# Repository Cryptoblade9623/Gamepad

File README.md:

# Gamepad
This is a keyboard with only 27 keys. It was designed for gaming, so only the keys that I need for games are included.
It has per-key RGB, and you can cycle through different animations with some combos I made.
It has a rotary encoder for volume control, and to mute something.
I am reusing many of the parts that I already have, so I will not include them in the BOM.
It is controlled and coded with CircuitPython with KMK and a Waveshare RP2040 Zero.
The files in the Files folder contain everything you need to make or edit it, like KiCad and Fusion 360 source files, Gerbers and firmware.

## BOM
| Item                     | Qty | Supplier   | Cost/item | Total Cost | link                                                                                                                                                                                                                                                                                                                                                                                                                                                                                                                                                                                                                                                                                                                                                                                                                                                                                                                           |
|--------------------------|-----|------------|-----------|------------|--------------------------------------------------------------------------------------------------------------------------------------------------------------------------------------------------------------------------------------------------------------------------------------------------------------------------------------------------------------------------------------------------------------------------------------------------------------------------------------------------------------------------------------------------------------------------------------------------------------------------------------------------------------------------------------------------------------------------------------------------------------------------------------------------------------------------------------------------------------------------------------------------------------------------------|
| Waveshare RP2040 Zero    | 1   | AliExpress | $3.22     | $3.22      | https://www.aliexpress.com/item/1005008738491752.html?spm=a2g0o.productlist.main.34.3f1d10600ni14G&algo_pvid=a21f30b3-3a94-43fc-8dde-88dda27b717c&algo_exp_id=a21f30b3-3a94-43fc-8dde-88dda27b717c-31&pdp_ext_f=%7B%22order%22%3A%22378%22%2C%22spu_best_type%22%3A%22price%22%2C%22eval%22%3A%221%22%2C%22fromPage%22%3A%22search%22%7D&pdp_npi=6%40dis%21USD%213.22%211.35%21%21%2121.38%218.96%21%4021613be817938165109603134e1081%2112000059443265566%21sea%21GB%210%21ABX%211%210%21n_tag%3A-29910%3Bd%3Ad6cd2d24%3Bm03_new_user%3A-29895%3BpisId%3A5000000218642851&curPageLogUid=lCmdrrr83lyW&utparam-url=scene%3Asearch%7Cquery_from%3A%7Cx_object_id%3A1005008738491752%7C_p_origin_prod%3A                                                                                                                                                                                                                           |
| SK6812 MINI E            | 1   | AliExpress | $3.89     | $3.89      | https://www.aliexpress.com/item/1005007804788253.html?spm=a2g0o.productlist.main.6.1a374166AxfWN4&algo_pvid=ce4f786e-61a2-4f07-85fa-2494f0c9bdd4&algo_exp_id=ce4f786e-61a2-4f07-85fa-2494f0c9bdd4-5&pdp_ext_f=%7B%22order%22%3A%2250%22%2C%22eval%22%3A%221%22%2C%22fromPage%22%3A%22search%22%7D&pdp_npi=6%40dis%21USD%213.89%213.89%21%21%213.89%213.89%21%402103810f17938167089143682e0d51%2112000042259509038%21sea%21GB%210%21ABX%211%210%21n_tag%3A-29910%3Bd%3Ad6cd2d24%3Bm03_new_user%3A-29895&curPageLogUid=SlNEr6LLqNnO&utparam-url=scene%3Asearch%7Cquery_from%3A%7Cx_object_id%3A1005007804788253%7C_p_origin_prod%3A                                                                                                                                                                                                                                                                                              |
| Custom PCB               | 1   | JLCPCB     | $10.90    | $10.90     | https://cart.jlcpcb.com/shopcart/cart/                                                                                                                                                                                                                                                                                                                                                                                                                                                                                                                                                                                                                                                                                                                                                                                                                                                                                         |
| 1N4148 Diodes            | 1   | AliExpress | $1.19     | $1.19      | https://www.aliexpress.com/item/1005007536719404.html?spm=a2g0o.detail.similar_items.1.d644K42vK42vpm&utparam-url=scene%3Aimage_search%7Cquery_from%3Aapp_pdp_sold_out%7Cx_object_id%3A1005007536719404%7C_p_origin_prod%3A&algo_pvid=a3281ef9-5730-48c4-893d-d7d506aeae6c&algo_exp_id=a3281ef9-5730-48c4-893d-d7d506aeae6c&pdp_ext_f=%7B%22order%22%3A%22306%22%2C%22spu_best_type%22%3A%22price%22%2C%22fromPage%22%3A%22search%22%7D&pdp_npi=6%40dis%21USD%211.28%211.19%21%21%218.53%217.93%21%4021613be817938177175121953e0fbc%2112000041199095476%21sea%21GB%210%21ABX%211%210%21n_tag%3A-29910%3Bd%3Ad6cd2d24%3Bm03_new_user%3A-29895%3BpisId%3A5000000220770329                                                                                                                                                                                                                                                        |
| USBC Breakout Board      | 1   | AliExpress | $1.13     | $1.13      | https://www.aliexpress.com/item/1005012011244259.html?spm=a2g0o.productlist.main.60.71a074621WW6ry&algo_pvid=724b5fb3-6e73-4c34-994f-f0d0a4bcf023&algo_exp_id=724b5fb3-6e73-4c34-994f-f0d0a4bcf023-57&pdp_ext_f=%7B%22order%22%3A%2267%22%2C%22eval%22%3A%221%22%2C%22fromPage%22%3A%22search%22%7D&pdp_npi=6%40dis%21USD%211.20%211.12%21%21%217.96%217.43%21%400b15841617938179246968172e0e1d%2112000057265199957%21sea%21GB%210%21ABX%211%210%21n_tag%3A-29910%3Bd%3Ad6cd2d24%3Bm03_new_user%3A-29895%3BpisId%3A5000000220770329&curPageLogUid=zSV1yswovQO5&utparam-url=scene%3Asearch%7Cquery_from%3A%7Cx_object_id%3A1005012011244259%7C_p_origin_prod%3A                                                                                                                                                                                                                                                                 |
| Stabilizers              | 1   | AliExpress | $4.51     | $4.51      | https://www.aliexpress.com/item/1005002003442544.html?spm=a2g0o.productlist.main.42.a17f2d96M7oa60&algo_pvid=f8edf524-10fd-4b72-87ca-8fe916213379&algo_exp_id=f8edf524-10fd-4b72-87ca-8fe916213379-37&pdp_ext_f=%7B%22order%22%3A%2256%22%2C%22eval%22%3A%221%22%2C%22fromPage%22%3A%22search%22%7D&pdp_npi=6%40dis%21USD%214.51%213.77%21%21%214.51%213.77%21%400b88ac1917939129812146151e0d1b%2112000033272651555%21sea%21GB%210%21ABX%211%210%21n_tag%3A-29910%3Bd%3Ad6cd2d24%3Bm03_new_user%3A-29895%3BpisId%3A5000000220905999&curPageLogUid=jusW35DST7r5&utparam-url=scene%3Asearch%7Cquery_from%3A%7Cx_object_id%3A1005002003442544%7C_p_origin_prod%3A                                                                                                                                                                                                                                                                 |
| Rubber Feet              | 1   | AliExpress | $1.23     | $1.23      | https://www.aliexpress.com/item/1005005828846290.html?spm=a2g0o.detail.pcDetailTopMoreOtherSeller.5.75ccCE3yCE3yFL&gps-id=pcDetailTopMoreOtherSeller&scm=1007.40050.354490.0&scm_id=1007.40050.354490.0&scm-url=1007.40050.354490.0&pvid=fc5e9689-4804-4616-a200-f08fdc2983ab&_t=gps-id%3ApcDetailTopMoreOtherSeller%2Cscm-url%3A1007.40050.354490.0%2Cpvid%3Afc5e9689-4804-4616-a200-f08fdc2983ab%2Ctpp_buckets%3A668%232846%238116%232002&pdp_ext_f=%7B%22order%22%3A%22466%22%2C%22eval%22%3A%221%22%2C%22sceneId%22%3A%2230050%22%2C%22fromPage%22%3A%22recommend%22%7D&pdp_npi=6%40dis%21USD%211.29%211.23%21%21%218.56%218.16%21%40210382de17939869266068634e0d1c%2112000034498446917%21rec%21GB%21%21ABX%211%210%21n_tag%3A-29910%3Bd%3Ad6cd2d24%3Bm03_new_user%3A-29895%3BpisId%3A5000000220905999&utparam-url=scene%3ApcDetailTopMoreOtherSeller%7Cquery_from%3A%7Cx_object_id%3A1005005828846290%7C_p_origin_prod%3A |
| Estimated total shipping |     |            |           | $6.66      |                                                                                                                                                                                                                                                                                                                                                                                                                                                                                                                                                                                                                                                                                                                                                                                                                                                                                                                                |
| Grand Total              |     |            |           | $32.73     |                                                                                                                                                                                                                                                                                                                                                                                                                                                                                                                                                                                                                                                                                                                                                                                                                                                                                                                                |

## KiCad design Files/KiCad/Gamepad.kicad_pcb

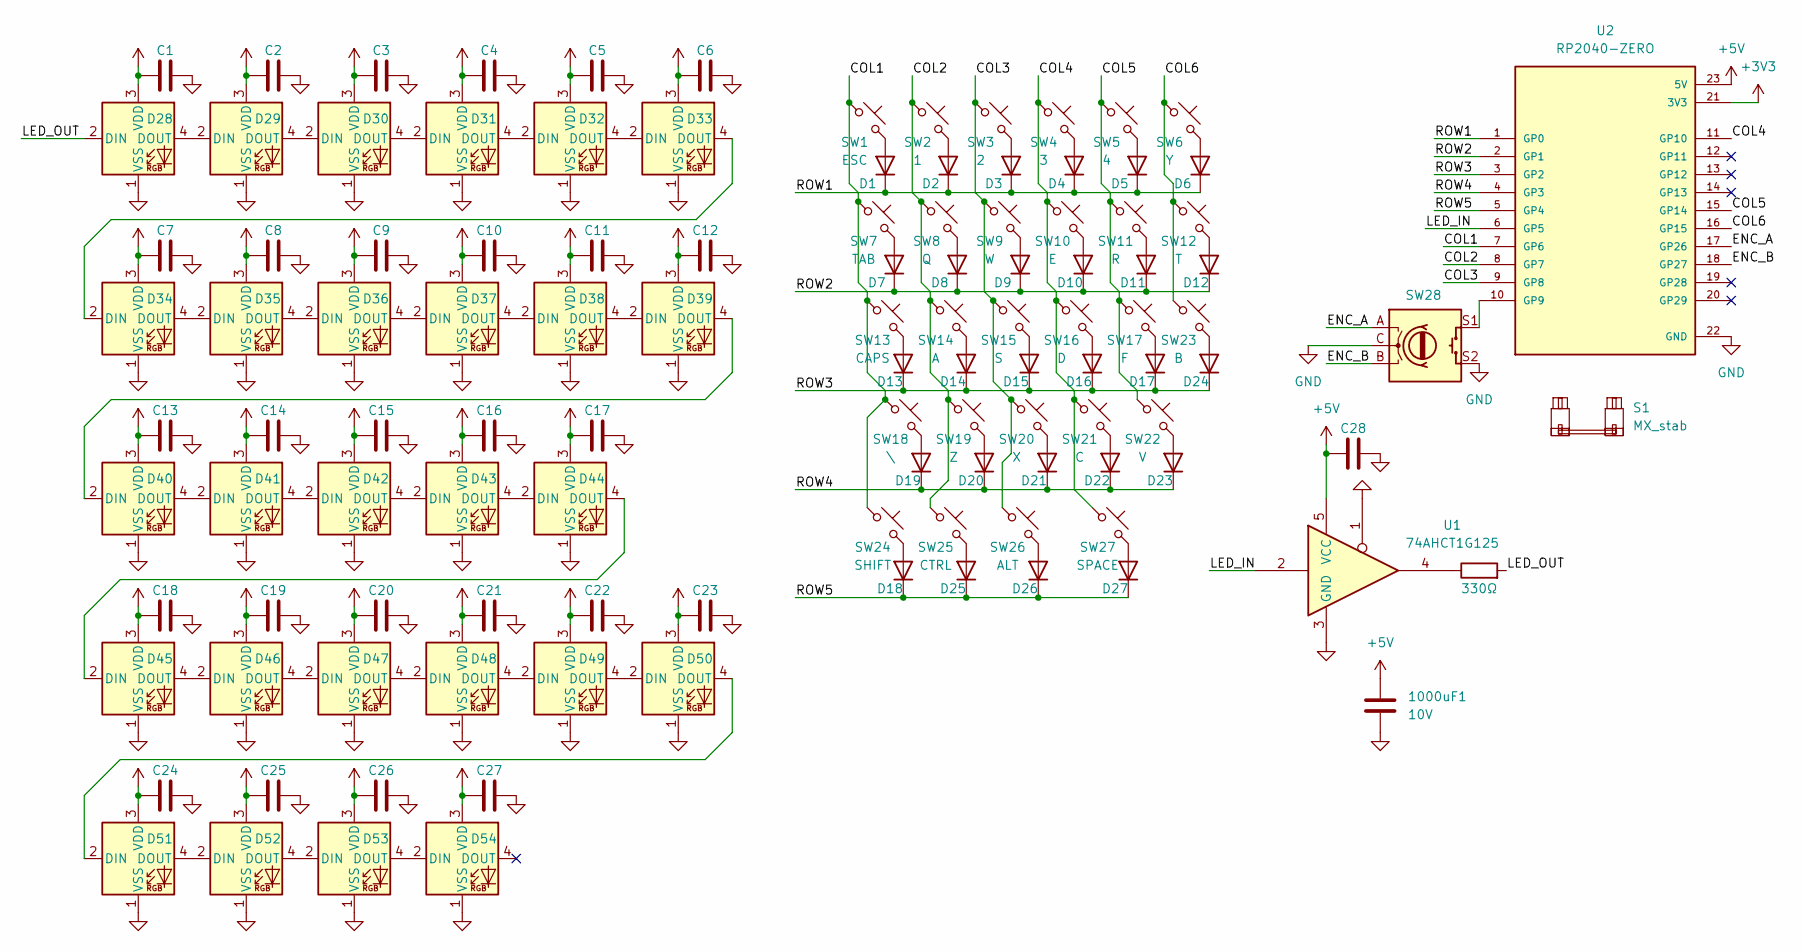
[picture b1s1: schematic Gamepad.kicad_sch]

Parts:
1000uF1: 10V; C_Radial_D12.5mm_H25.0mm_P5.00mm
C1, C2, C3, C4, C5, C6, C7, C8, C9, C10, C11, C12, C13, C14, C15, C16, C17, C18, C19, C20, C21, C22, C23, C24, C25, C26, C27, C28: C; C_0805_2012Metric_Pad1.18x1.45mm_HandSolder
D1, D2, D3, D4, D5, D6, D7, D8, D9, D10, D11, D12, D13, D14, D15, D16, D17, D18, D19, D20, D21, D22, D23, D24, D25, D26, D27: D; D_SOD-123
D28, D29, D30, D31, D32, D33, D34, D35, D36, D37, D38, D39, D40, D41, D42, D43, D44, D45, D46, D47, D48, D49, D50, D51, D52, D53, D54: SK6812MINI-E; LED_MX_6028R
R1: 330Ω; R_1206_3216Metric_Pad1.30x1.75mm_HandSolder
S1: MX_stab; STAB_MX_2.25u
SW1: ESC; SW_MX_1u
SW2: 1; SW_MX_1u
SW3: 2; SW_MX_1u
SW4: 3; SW_MX_1u
SW5: 4; SW_MX_1u
SW6: Y; SW_MX_1u
SW7: TAB; SW_MX_1.5u
SW8: Q; SW_MX_1u
SW9: W; SW_MX_1u
SW10: E; SW_MX_1u
SW11: R; SW_MX_1u
SW12: T; SW_MX_1u
SW13: CAPS; SW_MX_1.75u
SW14: A; SW_MX_1u
SW15: S; SW_MX_1u
SW16: D; SW_MX_1u
SW17: F; SW_MX_1u
SW18: \; SW_MX_1u
SW19: Z; SW_MX_1u
SW20: X; SW_MX_1u
SW21: C; SW_MX_1u
SW22: V; SW_MX_1u
SW23: B; SW_MX_1u
SW24: SHIFT; SW_MX_1u
SW25: CTRL; SW_MX_1.25u
SW26: ALT; SW_MX_1.25u
SW27: SPACE; SW_MX_1u
SW28: RotaryEncoder_Switch; RotaryEncoder_Alps_EC11E-Switch_Vertical_H20mm
U1: 74AHCT1G125; SOT-23-5_HandSoldering
U2: RP2040-ZERO; MODULE_RP2040-ZERO; PARTREV NA

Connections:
+3V3: U2.21 (3V3)
+5V: 1000uF1.1, C1.1, C2.1, C3.1, C4.1, C5.1, C6.1, C7.1, C8.1, C9.1, C10.1, C11.1, C12.1, C13.1, C14.1, C15.1, C16.1, C17.1, C18.1, C19.1, C20.1, C21.1, C22.1, C23.1, C24.1, C25.1, C26.1, C27.1, C28.1, D28.3 (VDD), D29.3 (VDD), D30.3 (VDD), D31.3 (VDD), D32.3 (VDD), D33.3 (VDD), D34.3 (VDD), D35.3 (VDD), D36.3 (VDD), D37.3 (VDD), D38.3 (VDD), D39.3 (VDD), D40.3 (VDD), D41.3 (VDD), D42.3 (VDD), D43.3 (VDD), D44.3 (VDD), D45.3 (VDD), D46.3 (VDD), D47.3 (VDD), D48.3 (VDD), D49.3 (VDD), D50.3 (VDD), D51.3 (VDD), D52.3 (VDD), D53.3 (VDD), D54.3 (VDD), U1.5 (VCC), U2.23 (5V)
/COL1: SW1.1, SW7.1, SW13.1, SW18.1, SW24.1, U2.7 (GP6)
/COL2: SW2.1, SW8.1, SW14.1, SW19.1, SW25.1, U2.8 (GP7)
/COL3: SW3.1, SW9.1, SW15.1, SW20.1, SW26.1, U2.9 (GP8)
/COL4: SW4.1, SW10.1, SW16.1, SW21.1, SW27.1, U2.11 (GP10)
/COL5: SW5.1, SW11.1, SW17.1, SW22.1, U2.15 (GP14)
/COL6: SW6.1, SW12.1, SW23.1, U2.16 (GP15)
/ENC_A: SW28.A, U2.17 (GP26)
/ENC_B: SW28.B, U2.18 (GP27)
/LED_IN: U1.2, U2.6 (GP5)
/LED_OUT: D28.2 (DIN), R1.2
/ROW1: D1.1 (K), D2.1 (K), D3.1 (K), D4.1 (K), D5.1 (K), D6.1 (K), U2.1 (GP0)
/ROW2: D7.1 (K), D8.1 (K), D9.1 (K), D10.1 (K), D11.1 (K), D12.1 (K), U2.2 (GP1)
/ROW3: D13.1 (K), D14.1 (K), D15.1 (K), D16.1 (K), D17.1 (K), D24.1 (K), U2.3 (GP2)
/ROW4: D19.1 (K), D20.1 (K), D21.1 (K), D22.1 (K), D23.1 (K), U2.4 (GP3)
/ROW5: D18.1 (K), D25.1 (K), D26.1 (K), D27.1 (K), U2.5 (GP4)
GND: 1000uF1.2, C1.2, C2.2, C3.2, C4.2, C5.2, C6.2, C7.2, C8.2, C9.2, C10.2, C11.2, C12.2, C13.2, C14.2, C15.2, C16.2, C17.2, C18.2, C19.2, C20.2, C21.2, C22.2, C23.2, C24.2, C25.2, C26.2, C27.2, C28.2, D28.1 (VSS), D29.1 (VSS), D30.1 (VSS), D31.1 (VSS), D32.1 (VSS), D33.1 (VSS), D34.1 (VSS), D35.1 (VSS), D36.1 (VSS), D37.1 (VSS), D38.1 (VSS), D39.1 (VSS), D40.1 (VSS), D41.1 (VSS), D42.1 (VSS), D43.1 (VSS), D44.1 (VSS), D45.1 (VSS), D46.1 (VSS), D47.1 (VSS), D48.1 (VSS), D49.1 (VSS), D50.1 (VSS), D51.1 (VSS), D52.1 (VSS), D53.1 (VSS), D54.1 (VSS), SW28.C, SW28.S2, U1.1, U1.3 (GND), U2.22 (GND)
unnamed: D1.2 (A), SW1.2
unnamed: D2.2 (A), SW2.2
unnamed: D3.2 (A), SW3.2
unnamed: D4.2 (A), SW4.2
unnamed: D5.2 (A), SW5.2
unnamed: D6.2 (A), SW6.2
unnamed: D7.2 (A), SW7.2
unnamed: D8.2 (A), SW8.2
unnamed: D9.2 (A), SW9.2
unnamed: D10.2 (A), SW10.2
unnamed: D11.2 (A), SW11.2
unnamed: D12.2 (A), SW12.2
unnamed: D13.2 (A), SW13.2
unnamed: D14.2 (A), SW14.2
unnamed: D15.2 (A), SW15.2
unnamed: D16.2 (A), SW16.2
unnamed: D17.2 (A), SW17.2
unnamed: D18.2 (A), SW24.2
unnamed: D19.2 (A), SW18.2
unnamed: D20.2 (A), SW19.2
unnamed: D21.2 (A), SW20.2
unnamed: D22.2 (A), SW21.2
unnamed: D23.2 (A), SW22.2
unnamed: D24.2 (A), SW23.2
unnamed: D25.2 (A), SW25.2
unnamed: D26.2 (A), SW26.2
unnamed: D27.2 (A), SW27.2
unnamed: D28.4 (DOUT), D29.2 (DIN)
unnamed: D29.4 (DOUT), D30.2 (DIN)
unnamed: D30.4 (DOUT), D31.2 (DIN)
unnamed: D31.4 (DOUT), D32.2 (DIN)
unnamed: D32.4 (DOUT), D33.2 (DIN)
unnamed: D33.4 (DOUT), D34.2 (DIN)
unnamed: D34.4 (DOUT), D35.2 (DIN)
unnamed: D35.4 (DOUT), D36.2 (DIN)
unnamed: D36.4 (DOUT), D37.2 (DIN)
unnamed: D37.4 (DOUT), D38.2 (DIN)
unnamed: D38.4 (DOUT), D39.2 (DIN)
unnamed: D39.4 (DOUT), D40.2 (DIN)
unnamed: D40.4 (DOUT), D41.2 (DIN)
unnamed: D41.4 (DOUT), D42.2 (DIN)
unnamed: D42.4 (DOUT), D43.2 (DIN)
unnamed: D43.4 (DOUT), D44.2 (DIN)
unnamed: D44.4 (DOUT), D45.2 (DIN)
unnamed: D45.4 (DOUT), D46.2 (DIN)
unnamed: D46.4 (DOUT), D47.2 (DIN)
unnamed: D47.4 (DOUT), D48.2 (DIN)
unnamed: D48.4 (DOUT), D49.2 (DIN)
unnamed: D49.4 (DOUT), D50.2 (DIN)
unnamed: D50.4 (DOUT), D51.2 (DIN)
unnamed: D51.4 (DOUT), D52.2 (DIN)
unnamed: D52.4 (DOUT), D53.2 (DIN)
unnamed: D53.4 (DOUT), D54.2 (DIN)
unnamed: R1.1, U1.4
unnamed: SW28.S1, U2.10 (GP9)

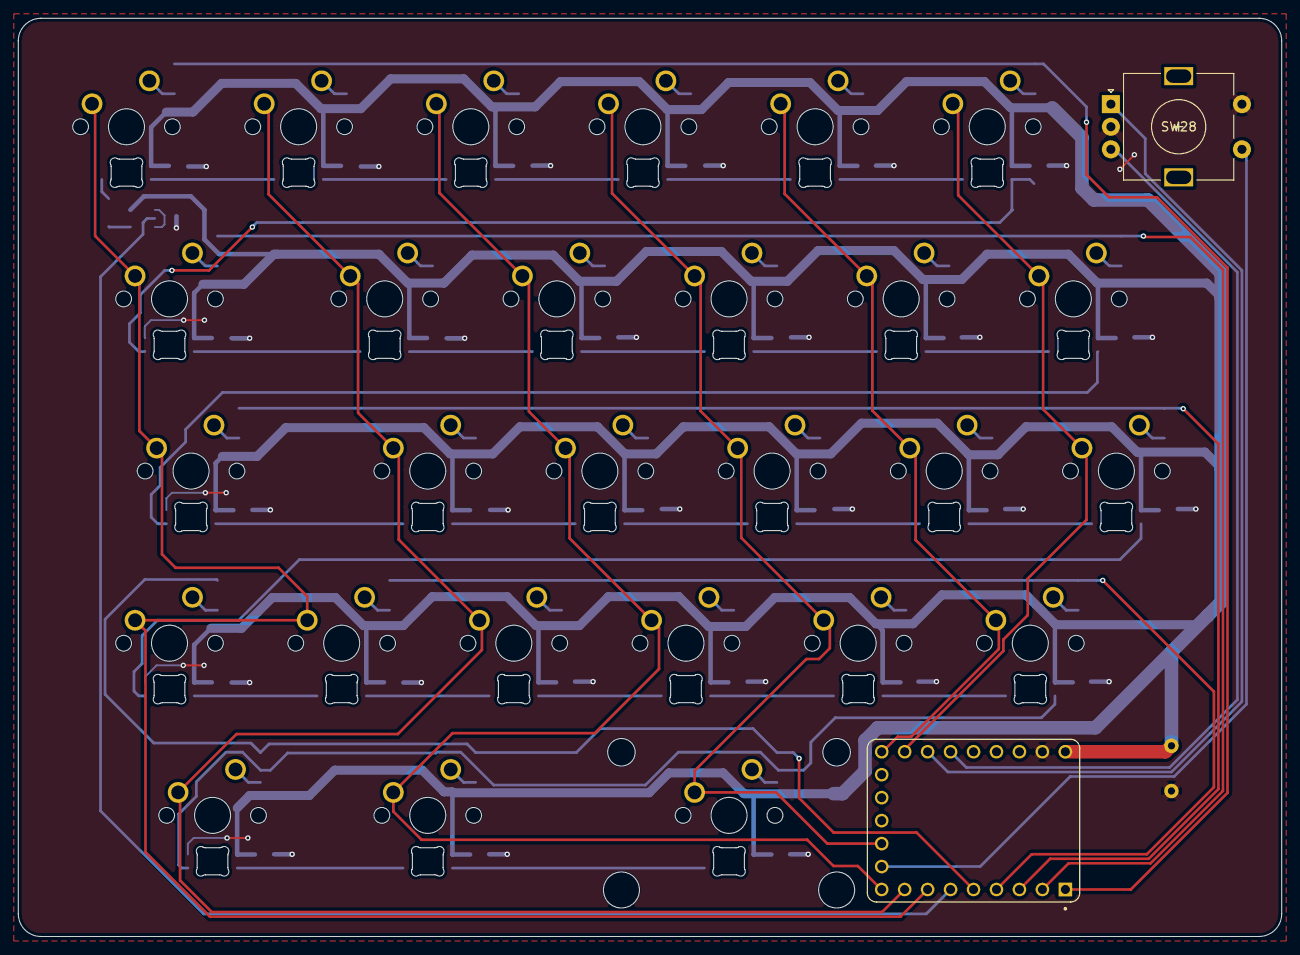
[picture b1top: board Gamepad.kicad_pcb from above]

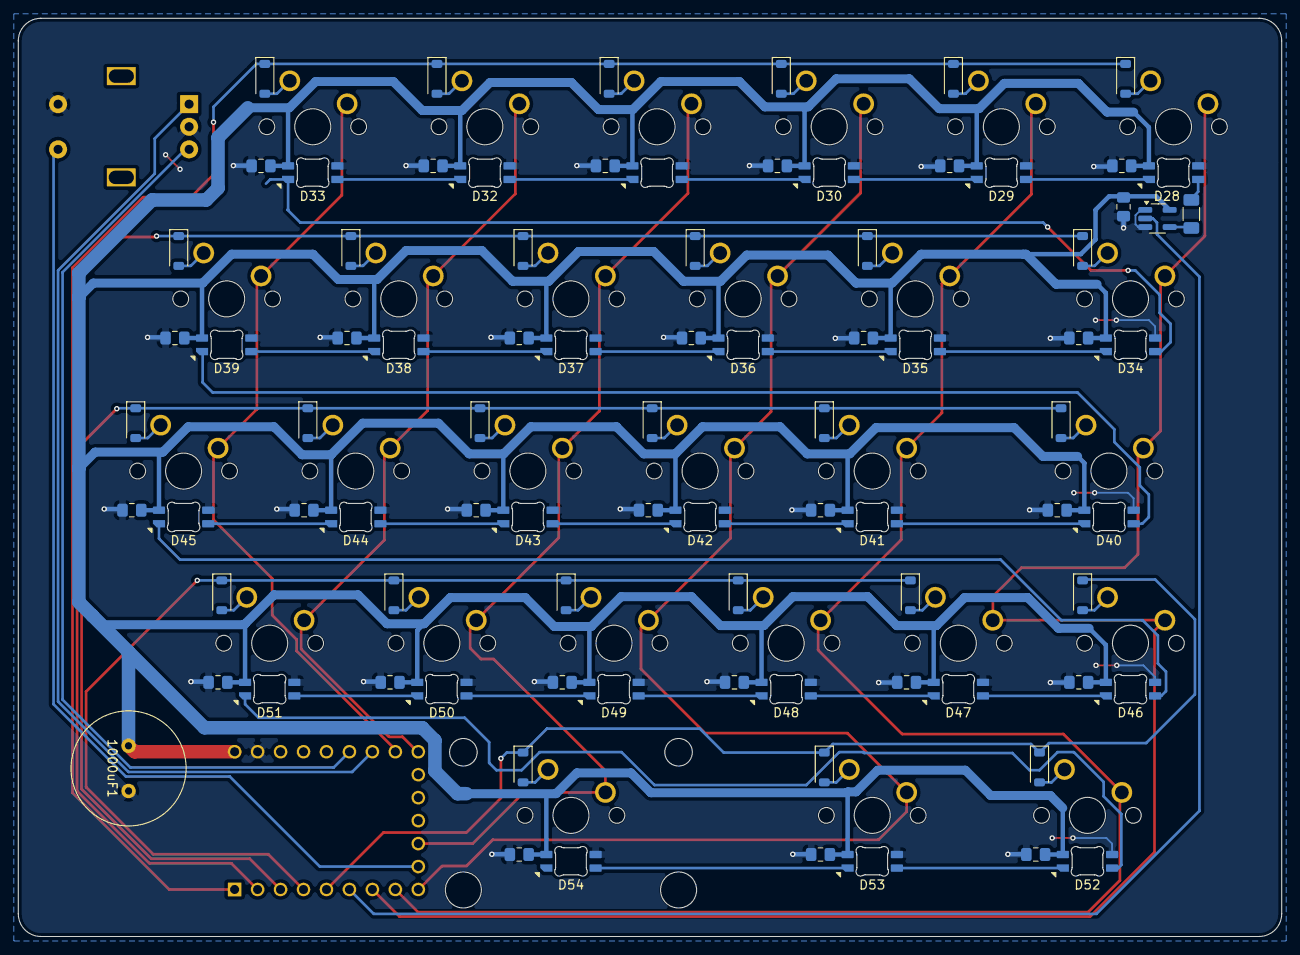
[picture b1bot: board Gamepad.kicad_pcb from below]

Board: 2 copper layers, 139.8 x 101.6 mm, 115 parts (85 on the bottom side), 72 nets.

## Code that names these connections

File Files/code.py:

print("Starting")
import board

from kmk.kmk_keyboard import KMKKeyboard
from kmk.keys import KC, make_key
from kmk.scanners import DiodeOrientation
from kmk.modules.encoder import EncoderHandler
from kmk.extensions.rgb import RGB
from kmk.extensions.rgb import AnimationModes
from kmk.modules.combos import Combos, Chord, Sequence

keyboard = KMKKeyboard()
combos = Combos()
KMKKeyboard.modules.append(combos)

#Defining MCU GPIO pins
COL1 = board.IO6
COL2 = board.IO7
COL3 = board.IO8
COL4 = board.IO10
COL5 = board.IO14
COL6 = board.IO15
ROW1 = board.IO0
ROW2 = board.IO1
ROW3 = board.IO2
ROW4 = board.IO3
ROW5 = board.IO4
MUTE = board.IO9
ENC_A = board.IO26
ENC_B = board.IO27
LED = board.IO5

#Defining the matrix dimensions and diode direction
keyboard.col_pins = (COL1,COL2,COL3,COL4,COL5,COL6)
keyboard.row_pins = (ROW1,ROW2,ROW3,ROW4,ROW5)
keyboard.diode_orientation = DiodeOrientation.COL2ROW

#Defining the keymap
keyboard.keymap = [
    [KC.ESC, KC.KP_1, KC.KP_2,KC.KP_3,KC.KP_4,KC.Y,
     KC.TAB, KC.Q, KC.W,KC.E,KC.R,KC.T,
     KC.CAPSLOCK,KC.A,KC.S,KC.D,KC.F,KC.B,
     KC.BSLASH,KC.Z,KC.X,KC.C,KC.V,KC.NO,
     KC.LSHIFT,KC.LCTRL,KC.LALT,KC.NO ,KC.SPACE,KC.NO,
    ]
]

#Defining the combos
combos.combos = [
    Chord((KC.LSHIFT, KC.TAB), KC.RGB_MOD),
    Chord((KC.LSHIFT, KC.ESC), KC.RGB_TOG),
]

#Defining encoder functions
encoder_handler = EncoderHandler()
keyboard.modules.append(encoder_handler)
encoder_handler.pins = ((ENC_A, ENC_B, MUTE, False),)
encoder_handler.map = (((KC.VOLD, KC.VOLU, KC.MUTE),),)

#Defining RBG patterns
rgb_ext = RGB(
    pixel_pin = LED,
    num_pixels = 6,
    val_limit = 100,
    val_default = 75,
    animation_speed = 1,
    animation_mode = AnimationModes.KNIGHT,
    refresh_rate = 50,
)
keyboard.extensions.append(rgb_ext)


if __name__ == '__main__':
    keyboard.go()
